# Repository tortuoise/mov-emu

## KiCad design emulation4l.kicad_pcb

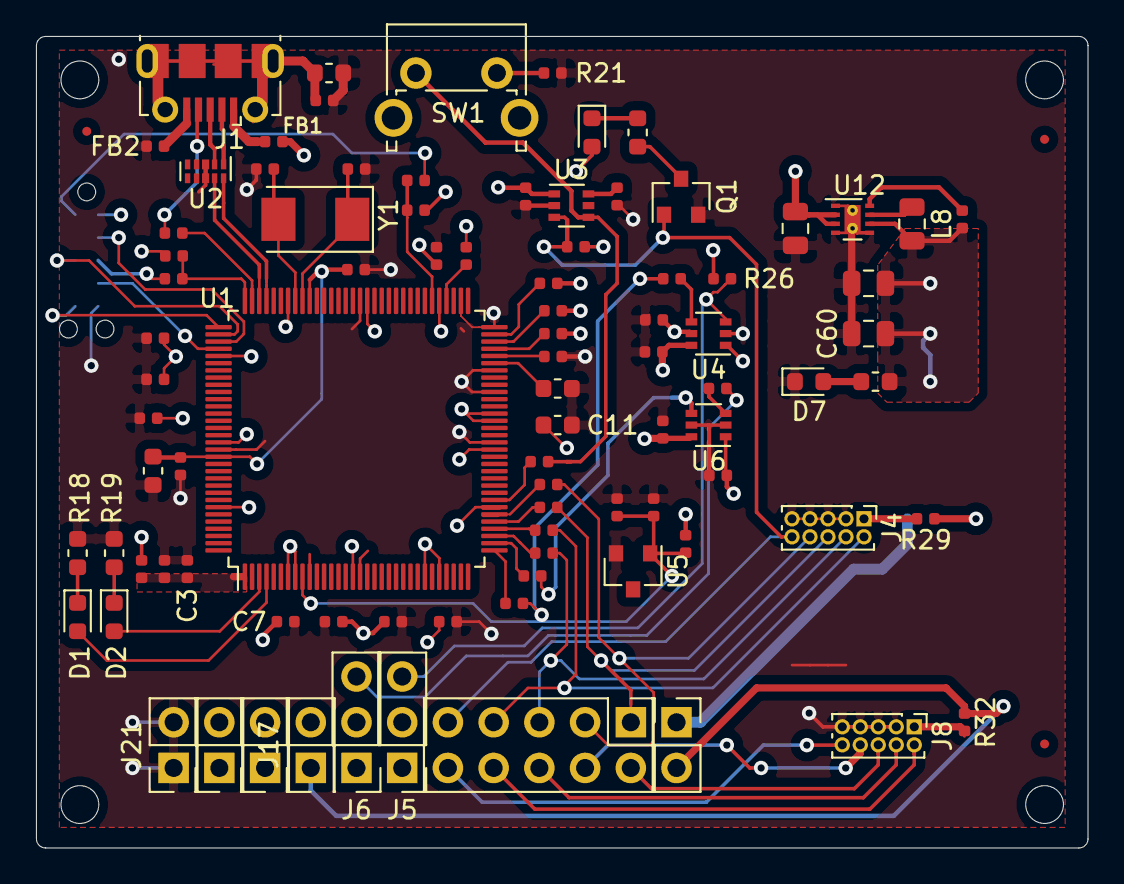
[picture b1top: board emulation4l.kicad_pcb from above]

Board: 4 copper layers, 58.4 x 45.1 mm, 93 parts (1 on the bottom side), 68 nets.

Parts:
C1, C2, C4, C5, C10, C14, C17, C19, C24, C25: 0.1u; C_0402_1005Metric
C3, C6, C7, C8, C9, C12, C13, C15, C16, C21: 0.01u; C_0402_1005Metric
C11: 0.1u; C_0603_1608Metric
C18: 2.2u; C_0603_1608Metric
C20, C22, C23: 1u; C_0402_1005Metric
C60, C62: 10u; C_0805_2012Metric
C61: 22u; C_0805_2012Metric
D1, D2, D3, D7: 150060YS75000; LED_0603_1608Metric
FB1, FB2: 10; C_0402_1005Metric
FID1, FID2, FID3: Fiducial; Fiducial_0.5mm_Mask1mm
J1: USB_B_Micro; USB_Micro-B_Molex-105017-0001
J3: Conn_02x05_Odd_Even; PinHeader_2x05_P2.54mm_Vertical
J4, J8: Conn_02x05_Odd_Even; PinHeader_2x05_P1.00mm_Vertical
J5, J6: Conn_01x03; PinHeader_1x03_P2.54mm_Vertical
J17, J18, J19, J20, J21: Conn_01x02; PinHeader_2x01_P2.54mm_Vertical
J22: Conn_02x05_Odd_Even; Tag-Connect_TC2050-IDC-NL_2x05_P1.27mm_Vertical
L8: L_Core_Iron_Small; L_0805_2012Metric
Q1: BSS138; SOT-23
R1, R2, R3, R4, R5, R6, R8, R27, R31: 33; R_0402_1005Metric
R7, R9, R10, R11, R25, R29, R32: 1k; R_0402_1005Metric
R12: 0; R_0402_1005Metric
R13, R21, R22: 100; R_0402_1005Metric
R14: 100k; R_0603_1608Metric
R15: 330k; R_0402_1005Metric
R16: 220k; R_0402_1005Metric
R17, R26, R146: 100k; R_0402_1005Metric
R18, R19: 220; R_0603_1608Metric
R20: 10k; R_0402_1005Metric
R23: 4.87k; R_0603_1608Metric
R24, R145: 270; R_0603_1608Metric
R28: 51; R_0402_1005Metric
SW1: SW_DIP_x01; SW_Tactile_SPST_Angled_PTS645Vx31-2LFS
U1: TM4C1294NCPDTI3R; LQFP-128_14x14mm_P0.4mm
U2: TPD4S010DQAR; USON-10_2.5x1.0mm_P0.5mm
U3, U4, U6: SN74LVC1T45DCK; SOT-363_SC-70-6
U5: LM4040DBZ-2.0; SOT-23
U12: TPS62162DSG; WSON-8-1EP_2x2mm_P0.5mm_EP0.9x1.6mm_ThermalVias
Y1: Crystal; Crystal_SMD_Abracon_ABM3-2Pin_5.0x3.2mm

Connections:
/CC_nRESET: J3.10, J8.10
/IRSTN: J22.2, R22.1
/ITCK: J22.7, U1.100
/ITDI: J22.6, U1.98
/ITDO: J22.10, U1.97
/ITMS: J22.3, U1.99
/P16_JTAG_TDI: J3.4, J8.8
/P17_JTAG_TDO: J3.2, J8.6
/P19_JTAG_TCK: J3.6, J8.4
/P20_JTAG_TMS: J3.8, J8.2
/VCC_BRD: J17.1, J18.2, R32.1
/VCC_LDO_3V3: C7.1, C8.1, C9.1, C10.1, C11.1, C12.1, C14.1, C15.2, C16.2, C23.2, C24.1, C60.1, C61.1, J17.2, J19.2, L8.2, R7.2, R9.2, R10.2, R20.1, R25.1, R28.2, R29.1, R145.1, R146.2, U1.7, U1.8, U1.16, U1.26, U1.28, U1.39, U1.47, U1.51, U1.52, U1.69, U1.79, U1.90, U1.101, U1.113, U1.122, U4.6, U6.6, U12.6
/VREFA: C21.1, C22.1, R25.2, U1.9, U5.1
/XDS_UART_RX: R1.2, R27.2
/XDS_UART_TX: R2.2, U6.4
GND: C1.1, C2.2, C3.1, C4.2, C5.2, C6.1, C7.2, C8.2, C9.2, C10.2, C11.2, C12.2, C13.1, C14.2, C15.1, C16.1, C17.1, C18.1, C19.1, C20.1, C21.2, C22.2, C23.1, C24.2, C25.1, C60.2, C61.2, C62.2, D7.1, FB2.2, J4.3, J4.5, J4.7, J4.9, J8.3, J8.5, J8.7, J8.9, J21.1, J21.2, J22.5, J22.9, Q1.2, R11.2, R14.2, R16.2, R18.1, R19.1, R21.2, R23.1, U1.48, U1.55, U1.58, U1.64, U1.66, U1.80, U1.114, U2.3, U3.2, U4.2, U5.2, U6.2, U6.5, U12.1, U12.4, U12.5, U12.9
unnamed: C1.2, R13.1, U1.96
unnamed: C2.1, J1.6, R14.1
unnamed: C3.2, R15.1, R16.1, U1.1
unnamed: C6.2, U1.88, Y1.1
unnamed: C13.2, U1.89, Y1.2
unnamed: C18.2, C19.2, C20.2, U1.87, U1.115
unnamed: D1.1, R18.2
unnamed: D1.2, U1.4
unnamed: D2.1, R19.2
unnamed: D2.2, U1.3
unnamed: D3.1, R24.2
unnamed: D7.2, R145.2
unnamed: FB1.2, J1.1
unnamed: FB2.1, J1.5
unnamed: J1.2, U2.1
unnamed: J1.3, U2.2
unnamed: J4.1, R29.2
unnamed: J5.3, R26.2, U4.3
unnamed: J6.3, R31.2
unnamed: J8.1, R32.2
unnamed: L8.1, U12.7
unnamed: Q1.3, R24.1
unnamed: R1.1, U1.33
unnamed: R2.1, U1.34
unnamed: R3.1, U1.35
unnamed: R4.1, U1.36
unnamed: R5.1, U1.37
unnamed: R6.1, U1.38
unnamed: R7.1, U1.63
unnamed: R8.1, U1.40
unnamed: R9.1, U1.62
unnamed: R10.1, U1.61
unnamed: R11.1, U1.60
unnamed: R12.1, U1.95
unnamed: R20.2, R22.2, U1.70
unnamed: R21.1, SW1.2
unnamed: R23.2, U1.59
unnamed: R27.1, U4.4
unnamed: R28.1, U1.68
unnamed: R31.1, U6.3
unnamed: R146.1, U12.8
VBUS_USB1: C62.1, FB1.1, J20.2, R13.2, R15.2, U12.2, U12.3
VCC_SENSE: C4.1, C17.2, C25.2, D3.2, J18.1, R17.1, R26.1, U3.1, U4.1, U4.5, U6.1
VCO_LDO_3V3: C5.1, U3.6
XDSET_DM: U1.93, U2.10
XDSET_DP: U1.94, U2.9
XDS_JTAG_TCK: J3.5, J4.4, R3.2
XDS_JTAG_TDI: J3.3, J4.8, R6.2
XDS_JTAG_TDO: J3.1, J4.6, R5.2
XDS_JTAG_TMS: J3.7, J4.2, R4.2
XDS_JTAG_nRESET: J3.9, J4.10, Q1.1, R17.2, U3.3
sw1: R8.2, SW1.1, U3.4

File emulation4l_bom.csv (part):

Source:,/home/sridhar/dev/kicad/cc3220s/emulation4l/emulation4l.sch,,,,,,,
Date:,Tue 12 Nov 2019 15:59:41 GMT,,,,,,,
Tool:,Eeschema 5.1.2-f72e74a~84~ubuntu18.04.1,,,,,,,
Generator:,/usr/share/kicad/plugins/bom_csv_grouped_by_value.py,,,,,,,
Component Count:,90,,,,,,,
,,,,,,,,
Individual Components:,,,,,,,,
,,,,,,,,
Item,Qty,Reference(s),Value,LibPart,Footprint,Datasheet,MFG Name,MFG Part Num
,,C1,0.1u,Device:C_Small,Capacitor_SMD:C_0402_1005Metric,~,TDK,C1005X5R1A104K050BA
,,C2,0.1u,Device:C_Small,Capacitor_SMD:C_0402_1005Metric,~,TDK,C1005X7R1C103K
,,C3,0.01u,Device:C_Small,Capacitor_SMD:C_0402_1005Metric,~,TDK,C1005X7R1C103K
,,C4,0.1u,Device:C_Small,Capacitor_SMD:C_0402_1005Metric,~,TDK,C1005X5R1A104K050BA
,,C5,0.1u,Device:C_Small,Capacitor_SMD:C_0402_1005Metric,~,TDK,C1005X5R1A104K050BA
,,C6,0.01u,Device:C_Small,Capacitor_SMD:C_0402_1005Metric,~,Murata,GRM1555C1H220FA01D
,,C7,0.01u,Device:C_Small,Capacitor_SMD:C_0402_1005Metric,~,TDK,C1005X7R1C103K
,,C8,0.01u,Device:C_Small,Capacitor_SMD:C_0402_1005Metric,~,TDK,C1005X7R1C103K
,,C9,0.01u,Device:C_Small,Capacitor_SMD:C_0402_1005Metric,~,TDK,C1005X7R1C103K
,,C10,0.1u,Device:C_Small,Capacitor_SMD:C_0402_1005Metric,~,AVX,06033D104KAT2A
,,C11,0.1u,Device:C_Small,Capacitor_SMD:C_0603_1608Metric,~,AVX,06033D104KAT2A
,,C12,0.01u,Device:C_Small,Capacitor_SMD:C_0402_1005Metric,~,TDK,C1005X5R1C105K050BC
,,C13,0.01u,Device:C_Small,Capacitor_SMD:C_0402_1005Metric,~,Murata,GRM1555C1H220FA01D
,,C14,0.1u,Device:C_Small,Capacitor_SMD:C_0402_1005Metric,~,TDK,C1005X5R1A104K050BA
,,C15,0.01u,Device:C_Small,Capacitor_SMD:C_0402_1005Metric,~,TDK,C1005X7R1C103K
,,C16,0.01u,Device:C_Small,Capacitor_SMD:C_0402_1005Metric,~,TDK,C1005X5R1C105K050BC
,,C17,0.1u,Device:C_Small,Capacitor_SMD:C_0402_1005Metric,~,TDK,C1005X5R1A104K050BA
,,C18,2.2u,Device:C_Small,Capacitor_SMD:C_0603_1608Metric,~,TDK,C1005X5R1C225K050BC
,,C19,0.1u,Device:C_Small,Capacitor_SMD:C_0402_1005Metric,~,AVX,06033D104KAT2A
,,C20,1u,Device:C_Small,Capacitor_SMD:C_0402_1005Metric,~,TDK,C1005X5R1C105K050BC
,,C21,0.01u,Device:C_Small,Capacitor_SMD:C_0402_1005Metric,~,TDK,C1005X7R1C103K
,,C22,1u,Device:C_Small,Capacitor_SMD:C_0402_1005Metric,~,TDK,C1005X5R1C105K050BC
,,C23,1u,Device:C_Small,Capacitor_SMD:C_0402_1005Metric,~,TDK,C1005X5R1C105K050BC
,,C24,0.1u,Device:C_Small,Capacitor_SMD:C_0402_1005Metric,~,TDK,C1005X5R1A104K050BA
,,C25,0.1u,Device:C_Small,Capacitor_SMD:C_0402_1005Metric,~,TDK,C1005X5R1A104K050BA
,,C60,10u,Device:C_Small,Capacitor_SMD:C_0805_2012Metric,~,Murata,GRM21BR61A106KE19L
,,C61,22u,Device:C_Small,Capacitor_SMD:C_0805_2012Metric,~,TDK,C2012X5R1C226K125AC
,,C62,10u,Device:C_Small,Capacitor_SMD:C_0805_2012Metric,~,Murata,GRM21BR61A106KE19L
,,D1,150060YS75000,LED:SFH4356P,LED_SMD:LED_0603_1608Metric,http://www.farnell.com/datasheets/1911348.pdf,Lumex,SML-LX0603GW-TR
,,D2,150060YS75000,LED:SFH4356P,LED_SMD:LED_0603_1608Metric,http://www.farnell.com/datasheets/1911348.pdf,Rohm,SML-311UTT86
,,D3,150060YS75000,LED:SFH4356P,LED_SMD:LED_0603_1608Metric,http://www.farnell.com/datasheets/1911348.pdf,Wurth Elektronik eiSos,150060YS75000
,,D7,150060YS75000,LED:SFH4356P,LED_SMD:LED_0603_1608Metric,http://www.farnell.com/datasheets/1911348.pdf,,
,,FB1,10,Device:Ferrite_Bead_Small,Capacitor_SMD:C_0402_1005Metric,~,Murata,BLM15AG100SN1D
,,FB2,10,Device:Ferrite_Bead_Small,Capacitor_SMD:C_0402_1005Metric,~,Murata,BLM15AG100SN1D
,,J1,USB_B_Micro,Connector:USB_B_Micro,Connector_USB:USB_Micro-B_Molex-105017-0001,~,Molex,105017-0001
,,J3,Conn_02x05_Odd_Even,Connector_Generic:Conn_02x05_Odd_Even,Connector_PinHeader_2.54mm:PinHeader_2x05_P2.54mm_Vertical,~,,
,,J4,Conn_02x05_Odd_Even,Connector_Generic:Conn_02x05_Odd_Even,Connector_PinHeader_1.00mm:PinHeader_2x05_P1.00mm_Vertical,~,Samtec,FTSH-105-01-F-D-K
,,J5,Conn_01x03,Connector_Generic:Conn_01x03,Connector_PinHeader_2.54mm:PinHeader_1x03_P2.54mm_Vertical,~,Wurth Elektronik,61300311121
,,J6,Conn_01x03,Connector_Generic:Conn_01x03,Connector_PinHeader_2.54mm:PinHeader_1x03_P2.54mm_Vertical,~,Wurth Elektronik,61300311121
,,J8,Conn_02x05_Odd_Even,Connector_Generic:Conn_02x05_Odd_Even,Connector_PinHeader_1.00mm:PinHeader_2x05_P1.00mm_Vertical,~,,
,,J17,Conn_01x02,Connector_Generic:Conn_01x02,Connector_PinHeader_2.54mm:PinHeader_2x01_P2.54mm_Vertical,~,Wurth Elektronik,61300211121
,,J18,Conn_01x02,Connector_Generic:Conn_01x02,Connector_PinHeader_2.54mm:PinHeader_2x01_P2.54mm_Vertical,~,Wurth Elektronik,61300211121
,,J19,Conn_01x02,Connector_Generic:Conn_01x02,Connector_PinHeader_2.54mm:PinHeader_2x01_P2.54mm_Vertical,~,Wurth Elektronik,61300211121
,,J20,Conn_01x02,Connector_Generic:Conn_01x02,Connector_PinHeader_2.54mm:PinHeader_2x01_P2.54mm_Vertical,~,Wurth Elektronik,61300211121
,,J21,Conn_01x02,Connector_Generic:Conn_01x02,Connector_PinHeader_2.54mm:PinHeader_2x01_P2.54mm_Vertical,~,Wurth Elektronik,61300211121
,,J22,Conn_02x05_Odd_Even,Connector_Generic:Conn_02x05_Odd_Even,pwrcon:Tag-Connect_TC2050-IDC-NL_2x05_P1.27mm_Vertical,~,Wurth Elektronik,61300311121
,,L8,L_Core_Iron_Small,Device:L_Core_Iron_Small,Inductor_SMD:L_0805_2012Metric,~,Taiyo Yuden,BRC2012T2R2MD
,,Q1,BSS138,Transistor_FET:BSS138,Package_TO_SOT_SMD:SOT-23,https://www.fairchildsemi.com/datasheets/BS/BSS138.pdf,Fairchild,BSS138
,,R1,33,Device:R,Resistor_SMD:R_0402_1005Metric,~,Panasonic,ERJ-2RKF33R0X
,,R2,33,Device:R,Resistor_SMD:R_0402_1005Metric,~,Panasonic,ERJ-2RKF33R0X
,,R3,33,Device:R,Resistor_SMD:R_0402_1005Metric,~,Panasonic,ERJ-2RKF33R0X
,,R4,33,Device:R,Resistor_SMD:R_0402_1005Metric,~,Panasonic,ERJ-2RKF33R0X
,,R5,33,Device:R,Resistor_SMD:R_0402_1005Metric,~,Panasonic,ERJ-2RKF33R0X
,,R6,33,Device:R,Resistor_SMD:R_0402_1005Metric,~,Panasonic,ERJ-2RKF33R0X
,,R7,1k,Device:R,Resistor_SMD:R_0402_1005Metric,~,Vishay-Dale,CRCW04021K00JNED
,,R8,33,Device:R,Resistor_SMD:R_0402_1005Metric,~,Panasonic,ERJ-2RKF33R0X
,,R9,1k,Device:R,Resistor_SMD:R_0402_1005Metric,~,Vishay-Dale,CRCW04021K00JNED
,,R10,1k,Device:R,Resistor_SMD:R_0402_1005Metric,~,Vishay-Dale,CRCW04021K00JNED
,,R11,1k,Device:R,Resistor_SMD:R_0402_1005Metric,~,Vishay-Dale,CRCW04021K00JNED
,,R12,0,Device:R,Resistor_SMD:R_0402_1005Metric,~,Panasonic,ERJ-2GE0R00X
,,R13,100,Device:R,Resistor_SMD:R_0402_1005Metric,~,Vishay-Dale,CRCW0402100RJNED
,,R14,100k,Device:R,Resistor_SMD:R_0603_1608Metric,~,Vishay-Dale,CRCW0603100KJNEA
,,R15,330k,Device:R,Resistor_SMD:R_0402_1005Metric,~,Vishay-Dale,CRCW0402330KJNED
,,R16,220k,Device:R,Resistor_SMD:R_0402_1005Metric,~,Vishay-Dale,CRCW0402220KJNED
,,R17,100k,Device:R,Resistor_SMD:R_0402_1005Metric,~,Vishay-Dale,CRCW0402100KJNED
,,R18,220,Device:R,Resistor_SMD:R_0603_1608Metric,~,Vishay-Dale,CRCW0603220RJNEA
,,R19,220,Device:R,Resistor_SMD:R_0603_1608Metric,~,Vishay-Dale,CRCW0603220RJNEA
,,R20,10k,Device:R,Resistor_SMD:R_0402_1005Metric,~,Vishay-Dale,CRCW040210K0JNED
,,R21,100,Device:R,Resistor_SMD:R_0402_1005Metric,~,Panasonic,ERJ-2RKF1000X
,,R22,100,Device:R,Resistor_SMD:R_0402_1005Metric,~,Vishay-Dale,CRCW0402100RFKED
,,R23,4.87k,Device:R,Resistor_SMD:R_0603_1608Metric,~,Vishay-Dale,CRCW06034K87FKEA
,,R24,270,Device:R,Resistor_SMD:R_0603_1608Metric,~,Vishay-Dale,CRCW0603270RJNEA
,,R25,1k,Device:R,Resistor_SMD:R_0402_1005Metric,~,Vishay-Dale,CRCW04021K00JNED
,,R26,100k,Device:R,Resistor_SMD:R_0402_1005Metric,~,Vishay-Dale,CRCW0402100KJNED
,,R27,33,Device:R,Resistor_SMD:R_0402_1005Metric,~,Panasonic,ERJ-2RKF33R0X
,,R28,51,Device:R,Resistor_SMD:R_0402_1005Metric,~,Vishay-Dale,CRCW040251R0JNED
,,R29,1k,Device:R,Resistor_SMD:R_0402_1005Metric,~,Vishay-Dale,CRCW04021K00JNED
,,R31,33,Device:R,Resistor_SMD:R_0402_1005Metric,~,Panasonic,ERJ-2RKF33R0X
,,R32,1k,Device:R,Resistor_SMD:R_0402_1005Metric,~,Vishay-Dale,CRCW04021K00JNED
,,R145,270,Device:R,Resistor_SMD:R_0603_1608Metric,~,Vishay-Dale,CRCW0603270RJNEA
,,R146,100k,Device:R,Resistor_SMD:R_0402_1005Metric,~,Vishay-Dale,CRCW0402100KJNED
,,SW1,SW_DIP_x01,Switch:SW_DIP_x01,Button_Switch_THT:SW_Tactile_SPST_Angled_PTS645Vx31-2LFS,~,APEM,MJTP1117
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
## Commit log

2019-11-13 Fixes for Aisler
